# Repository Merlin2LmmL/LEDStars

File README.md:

# LEDStars

A snowflake-shaped Christmas ornament that is its own circuit board. It hangs on a tree branch, has 25 LEDs and runs
on a coin cell. I'm making about ten of them as Christmas presents for my family.

License: CERN-OHL-S-2.0 · Author: Merlin2LmmL

*A Blender render of the ornament hanging from a fir twig. You're looking at the back of the board, where the light comes out. More colours and angles are in the [gallery](#gallery).*

## What it is

Five arms with five LEDs each (red, yellow, white, blue and green), a CH32V003 microcontroller in the middle and a CR2032
holder. The LEDs are reverse-mount parts: they sit on the front of the board and shine through a small hole in the PCB,
so from the back you only see glowing dots. The battery, chip and everything else stay on the side that faces the tree.

- **Microcontroller:** WCH CH32V003F4P6, a tiny 48 MHz RISC-V chip in a TSSOP-20.
- **LEDs:** 25 XL-3216 reverse-mount LEDs (1206). The chip lights one arm at a time and cycles through them quickly, so 25 LEDs don't need 25 pins. Each colour has its own resistor because the colours need different currents.
- **Power:** a CR2032 in an SMD holder, with a 100 nF capacitor next to the chip.
- **Controls:** a button to change the lighting mode and a three-position slide switch for on, off and clock.
- **Programming:** three bare pads for SWIO (`J1`). There is no header, you just hold jumper wires on the pads while flashing with a WCH-LinkE.
- **Size:** about 99 × 95 mm, just under JLCPCB's 100 × 100 mm limit, with a hang hole in the top arm.
- **3D model:** [`hardware/LEDStar.step`](hardware/LEDStar.step), the full assembled board with all components, exported from KiCad. There is no case or other mechanical part, so the CAD source is the KiCad project in [`hardware/`](hardware/) ([`LEDStars.kicad_pcb`](hardware/LEDStars.kicad_pcb), [`LEDStars.kicad_sch`](hardware/LEDStars.kicad_sch) and [`LEDStars.kicad_pro`](hardware/LEDStars.kicad_pro)).

It's still only a design. No board has been ordered yet and there's no firmware in this repo.

## Gallery

Open a colour set and click any picture for the full-size image (2400 × 1600). Every set has a front, a left and a right view.

<details open>
<summary><b>White + yellow</b></summary>

<p>

</p>
<p><i>front · left · right</i></p>

</details>

<details>
<summary><b>White + blue</b></summary>

<p>

</p>
<p><i>front · left · right</i></p>

</details>

<details>
<summary><b>Red + green</b></summary>

<p>

</p>
<p><i>front · left · right</i></p>

</details>

### How the renders are made

The board comes straight from the KiCad file (`kicad-cli pcb export glb`). The tree is built from the CC0 *Fir Sapling*
scans by [Poly Haven](https://polyhaven.com/a/fir_sapling). The ornament isn't posed by hand: it's a rigid body with
gravity, hanging on a simulated string that runs through the hang hole and over a real twig. Each image is rendered in
Blender 4.5 (Cycles, 512 samples, OpenImageDenoise) and takes about three minutes on my RX 9070 XT.

| File | What |
|---|---|
| [`render/gallery/`](render/gallery/) | the 9 final images |
| [`LEDStar_hanging_physics.blend`](https://github.com/Merlin2LmmL/LEDStars/releases/latest/download/LEDStar_hanging_physics.blend) | the Blender scene (82 MB, on the [Releases](https://github.com/Merlin2LmmL/LEDStars/releases) page). Open it in Blender 4.5 or newer and press Play to watch the ornament drop and settle |
| [`render/scene.py`](render/scene.py) | builds the whole scene from the board export |
| [`render/README.md`](render/README.md) | how to rebuild it, plus credits |

## Build journal

I wrote down how the project went in [`JOURNAL.md`](JOURNAL.md): what I tried, what I changed my mind about and why.
It reads best from the top, since the entries are in the order things happened. If a later entry contradicts an
earlier one, the later one is right (I changed the chip, for example).

| # | Entry | What it covers |
|---|---|---|
| 1 | [November 17, 2026: Getting the Idea](JOURNAL.md#november-17-2026-getting-the-idea) | Why a snowflake ornament as a gift, and what existing kits looked like |
| 2 | [November 17, 2026 (entry 2): Deciding what the star has to be](JOURNAL.md#november-17-2026-entry-2-deciding-what-the-star-has-to-be) | The requirements: coin cell, no recharging, no through-hole parts, and the first chip (ATtiny404) |
| 3 | [November 17, 2026 (entry 3): Reconsidering my life choises](JOURNAL.md#november-17-2026-entry-3-reconsidering-my-life-choises) | Checking the parts catalogue and switching to the CH32V003 |
| 4 | [November 17, 2026 (entry 4): Deciding on the PCB Outline and LED ordering](JOURNAL.md#november-17-2026-entry-4-deciding-on-the-pcb-outline-and-led-ordering) | The board outline, LED colour order and net classes |
| 5 | [November 17, 2026 (entry 5): Routing the first version](JOURNAL.md#november-17-2026-entry-5-routing-the-first-version) | Placing the parts and routing the first version |
| 6 | [November 17, 2026 (entry 6): Letting the LEDs shine through the board](JOURNAL.md#november-17-2026-entry-6-letting-the-leds-shine-through-the-board) | Reverse-mount LEDs that shine through the board |
| 7 | [November 17, 2026 (entry 7): Reconsidering my life choises ... part 2](JOURNAL.md#november-17-2026-entry-7-reconsidering-my-life-choises--part-2) | Turning the star into a snowflake |
| 8 | [November 17, 2026 (entry 8): Back silkscreen, the repo and JLCPCB being a pain in the ass](JOURNAL.md#november-17-2026-entry-8-back-silkscreen-the-repo-and-jlcpcb-being-a-pain-in-the-ass) | Back silkscreen, the repo, and JLCPCB's Economic assembly saying no |
| 9 | [November 17, 2026 (entry 9): Doing some heavy blender rendering](JOURNAL.md#november-17-2026-entry-9-doing-some-heavy-blender-rendering) | The physics-based Blender renders |
| 10 | [November 18, 2026: Added 3 pos switch and mode switch](JOURNAL.md#november-18-2026-added-3-pos-switch-and-mode-switch) | The mode button and the ON / OFF / CLOCK slide switch I forgot at first |

## License

[CERN-OHL-S-2.0](LICENSE). If you build on this design, share your changes under the same license.

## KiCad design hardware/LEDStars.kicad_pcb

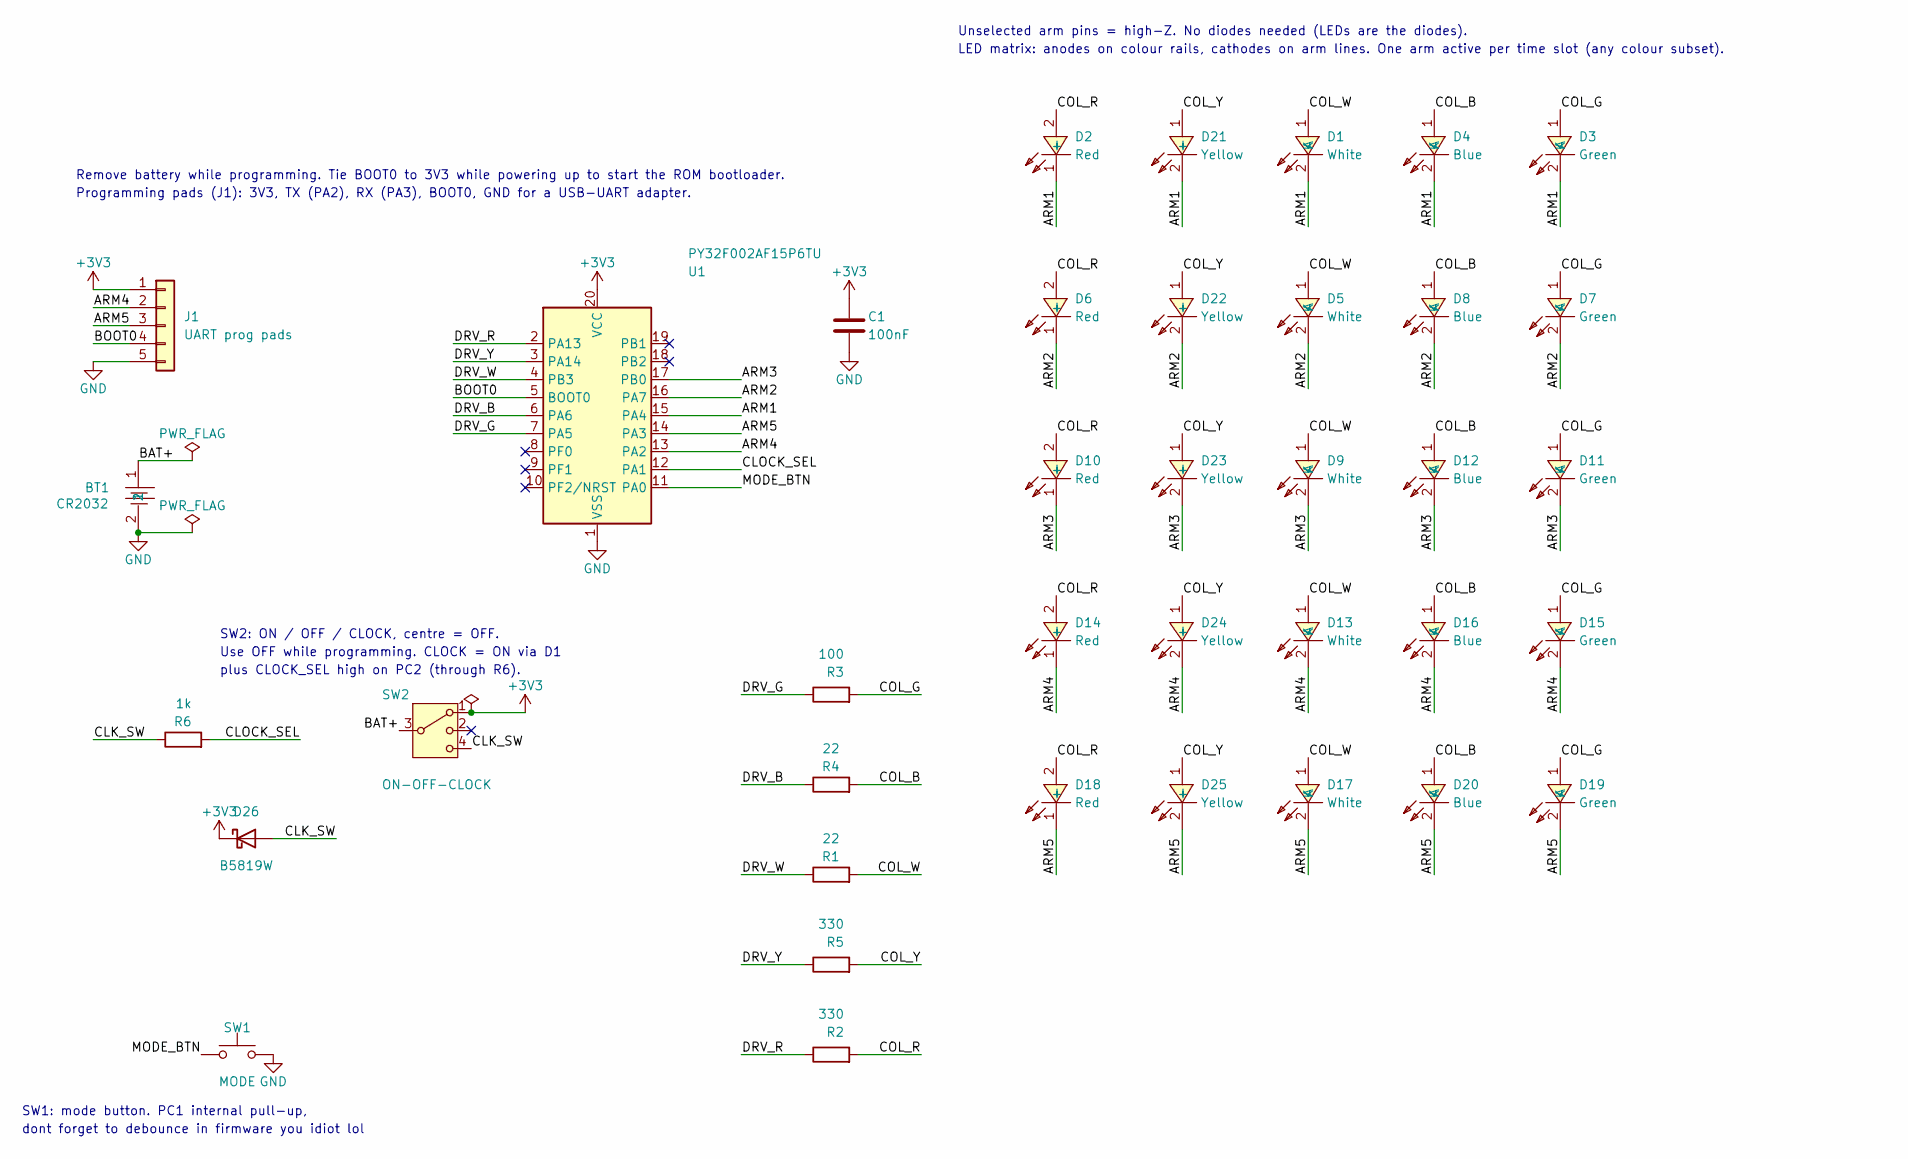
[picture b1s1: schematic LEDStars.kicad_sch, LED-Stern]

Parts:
BT1: CR2032; BAT-SMD_BS-10-B2AA010; MPN BS-10-B2AA010; LCSC Part C964798
C1: 100nF; C0603; Tolerance 10%; Voltage 50V; MPN CC0603KRX7R9BB104; LCSC Part C14663
D1, D5, D9, D13, D17: White; LED1206-RM_XL-3216; MPN KT-0805W; LCSC Part C3646935
D2, D6, D10, D14, D18: Red; LED1206-RM_XL-3216_K1; MPN NCD0805R1; LCSC Part C3646938
D3, D7, D11, D15, D19: Green; LED1206-RM_XL-3216; MPN KT-0805G; LCSC Part C3646937
D4, D8, D12, D16, D20: Blue; LED1206-RM_XL-3216; MPN KT-0805B; LCSC Part C3646941
D21, D22, D23, D24, D25: Yellow; LED1206-RM_XL-3216; MPN KT-0805Y; LCSC Part C3646939
D26: B5819W; D_SOD-123; MPN B5819W SL; LCSC Part C8598
J1: UART prog pads; UART_Pads_1x05_Staggered
R1, R4: 22; R0603; Tolerance 1%; Voltage 75V; MPN 0603WAF220JT5E; LCSC Part C23345
R2, R5: 330; R0603; Tolerance 1%; Voltage 75V; MPN 0603WAF3300T5E; LCSC Part C23138
R3: 100; R0603; Tolerance 1%; Voltage 75V; MPN 0603WAF1000T5E; LCSC Part C22775
R6: 1k; R0603; MPN 0603WAF1001T5E; LCSC Part C21190
SW1: MODE; KEY-SMD_L4.0-W3.0-LS4.9-1; MPN 3x4x2-2P-1.6N; LCSC Part C49234124
SW2: ON-OFF-CLOCK; SW-SMD_MSK13C02-SZ; MPN MSK13C02; LCSC Part C2681567
U1: PY32F002AF15P6TU; TSSOP-20_L6.5-W4.4-P0.65-LS6.4-BL; MPN PY32F002AF15P6TU; LCSC Part C5292059

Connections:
/ARM1: D1.2 (K), D2.1 (-), D3.2 (K), D4.2 (K), D21.2 (-), U1.15 (PA4)
/ARM2: D5.2 (K), D6.1 (-), D7.2 (K), D8.2 (K), D22.2 (-), U1.16 (PA7)
/ARM3: D9.2 (K), D10.1 (-), D11.2 (K), D12.2 (K), D23.2 (-), U1.17 (PB0)
/ARM4: D13.2 (K), D14.1 (-), D15.2 (K), D16.2 (K), D24.2 (-), J1.2, U1.13 (PA2)
/ARM5: D17.2 (K), D18.1 (-), D19.2 (K), D20.2 (K), D25.2 (-), J1.3, U1.14 (PA3)
/BOOT0: J1.4, U1.5 (BOOT0)
/CLK_SW: D26.2 (A), R6.1, SW2.4
/CLOCK_SEL: R6.2, U1.12 (PA1)
/COL_B: D4.1 (A), D8.1 (A), D12.1 (A), D16.1 (A), D20.1 (A), R4.2
/COL_G: D3.1 (A), D7.1 (A), D11.1 (A), D15.1 (A), D19.1 (A), R3.2
/COL_R: D2.2 (+), D6.2 (+), D10.2 (+), D14.2 (+), D18.2 (+), R2.2
/COL_W: D1.1 (A), D5.1 (A), D9.1 (A), D13.1 (A), D17.1 (A), R1.2
/COL_Y: D21.1 (+), D22.1 (+), D23.1 (+), D24.1 (+), D25.1 (+), R5.2
/DRV_B: R4.1, U1.6 (PA6)
/DRV_G: R3.1, U1.7 (PA5)
/DRV_R: R2.1, U1.2 (PA13)
/DRV_W: R1.1, U1.4 (PB3)
/DRV_Y: R5.1, U1.3 (PA14)
/MODE_BTN: SW1.1, U1.11 (PA0)

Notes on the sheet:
LED matrix: anodes on colour rails, cathodes on arm lines. One arm active per time slot (any colour subset).
SW2: ON / OFF / CLOCK, centre = OFF.
SW1: mode button. PC1 internal pull-up,
Use OFF while programming. CLOCK = ON via D1
plus CLOCK_SEL high on PC2 (through R6).
Programming pads (J1): 3V3, TX (PA2), RX (PA3), BOOT0, GND for a USB-UART adapter.
Remove battery while programming. Tie BOOT0 to 3V3 while powering up to start the ROM bootloader.
dont forget to debounce in firmware you idiot lol
Unselected arm pins = high-Z. No diodes needed (LEDs are the diodes).

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
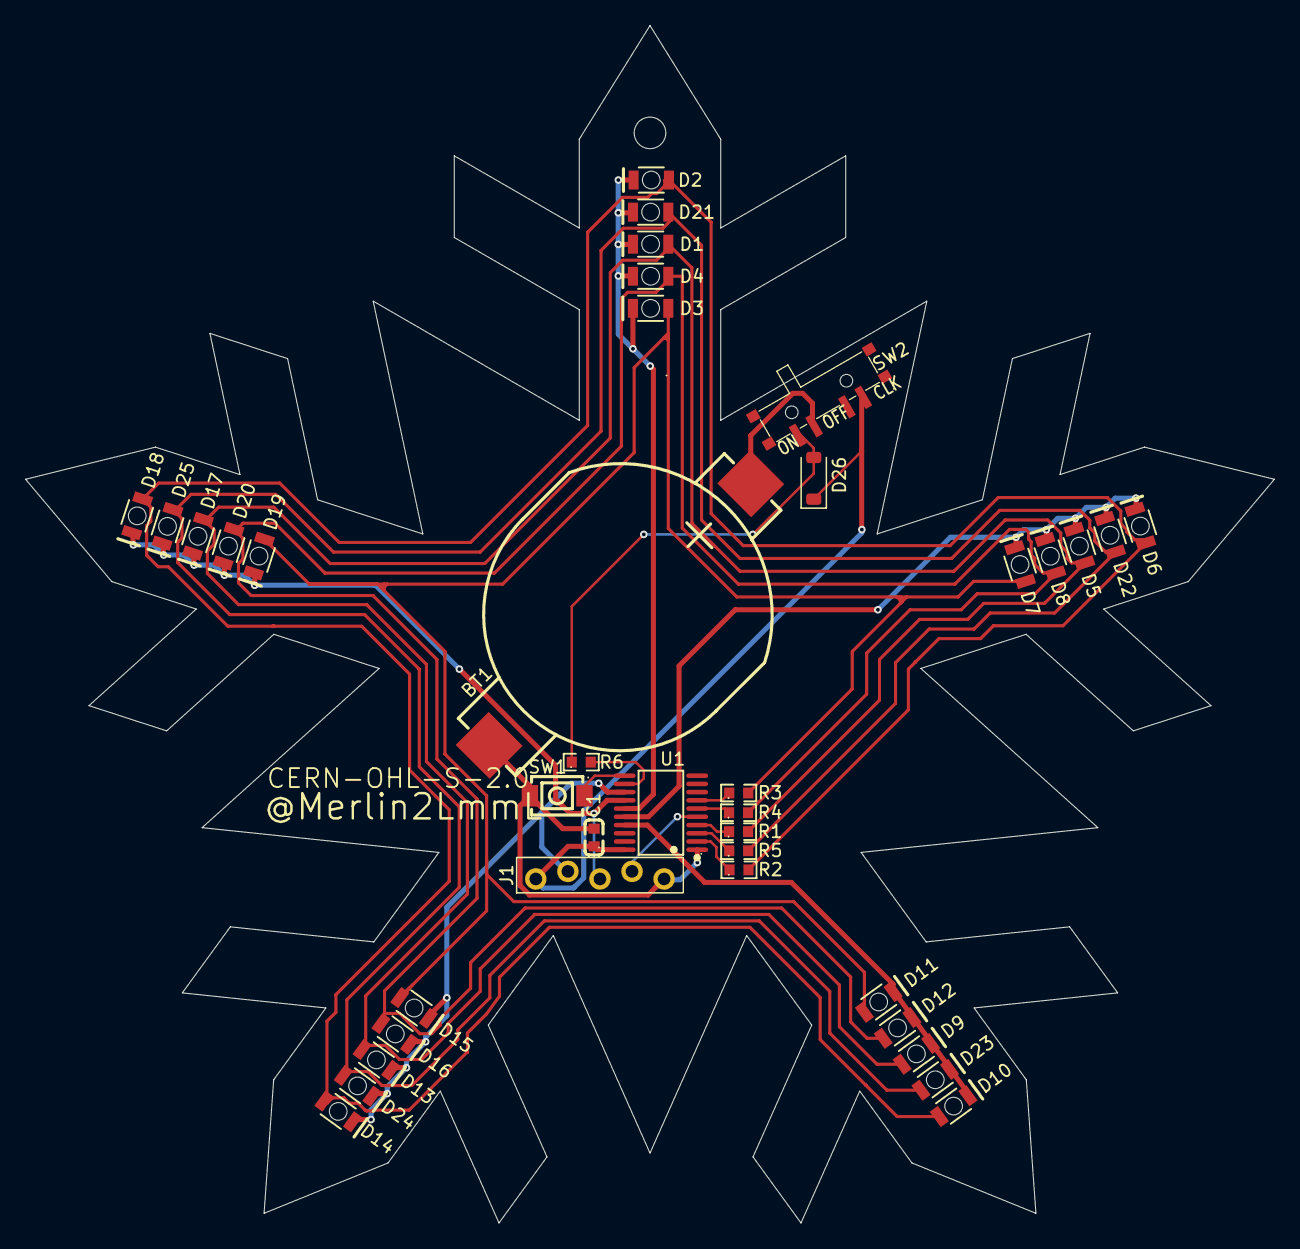
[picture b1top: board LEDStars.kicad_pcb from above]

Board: 2 copper layers, 98.9 x 94.8 mm, 38 parts (0 on the bottom side), 22 nets.

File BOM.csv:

References,Description,Vendor,MPN,LCSC,JLC class,Qty per board,Qty for 10 boards,Unit price USD (est.),Line total USD (est.),Link
-,"PCB, white solder mask, 1.6 mm, OSP (JLCPCB, order LEDStars_Y20)",JLCPCB,,,,1,10,1.50,15.00,https://jlcpcb.com/
-,Solder paste Sn99Ag0.3Cu0.7 (35 g) + flux (10 g) bundle,AliExpress,,,,1,1,EUR 11.19,EUR 11.19,https://de.aliexpress.com/item/1005009348891918.html
U1,"Microcontroller, RISC-V, TSSOP-20",LCSC,CH32V003F4P6,C5187096,Extended,1,10,0.3085,3.08,https://www.lcsc.com/product-detail/C5187096.html
BT1,"CR2032 battery holder, SMD",LCSC,BS-10-B2AA010,C964798,Extended,1,10,0.4598,4.60,https://www.lcsc.com/product-detail/C964798.html
"D1, D5, D9, D13, D17","White LED, reverse-mount 1206",LCSC,XL-3216UWC-FB,C3646935,Extended,5,50,0.0165,0.83,https://www.lcsc.com/product-detail/C3646935.html
"D21, D22, D23, D24, D25","Yellow LED, reverse-mount 1206",LCSC,XL-3216UYC-FB,C3646939,Extended,5,50,0.0159,0.80,https://www.lcsc.com/product-detail/C3646939.html
"D2, D6, D10, D14, D18","Red LED, reverse-mount 1206",LCSC,XL-3216SURC-FB,C3646938,Extended,5,50,0.0105,0.53,https://www.lcsc.com/product-detail/C3646938.html
"D3, D7, D11, D15, D19","Green LED, reverse-mount 1206",LCSC,XL-3216UGC-FB,C3646937,Extended,5,50,0.0101,0.51,https://www.lcsc.com/product-detail/C3646937.html
"D4, D8, D12, D16, D20","Blue LED, reverse-mount 1206",LCSC,XL-3216UBC-FB,C3646941,Extended,5,50,0.0146,0.73,https://www.lcsc.com/product-detail/C3646941.html
SW2,3-position slide switch (ON / OFF / CLOCK),LCSC,MSK13C02,C2681567,Extended,1,10,0.1169,1.17,https://www.lcsc.com/product-detail/C2681567.html
SW1,"Tactile button (mode), 3x4 mm",LCSC,HX 3x4x2-2P-1.6N TACTILE SWITCH,C49234124,Extended,1,10,0.0254,0.25,https://www.lcsc.com/product-detail/C49234124.html
D26,Schottky diode 40 V 1 A (CLOCK position power),LCSC,B5819W SL,C8598,Basic,1,10,0.0262,0.26,https://www.lcsc.com/product-detail/C8598.html
C1,100 nF 50 V X7R 0603 capacitor,LCSC,CL10B104KB8NNNC,C1591,Extended,1,10,0.0071,0.07,https://www.lcsc.com/product-detail/C1591.html
"R1, R4",22 Ω 0603 resistor,LCSC,0603WAF220JT5E,C23345,Basic,2,20,0.0017,0.03,https://www.lcsc.com/product-detail/C23345.html
R3,100 Ω 0603 resistor,LCSC,0603WAF1000T5E,C22775,Basic,1,10,0.0023,0.02,https://www.lcsc.com/product-detail/C22775.html
"R2, R5",330 Ω 0603 resistor,LCSC,0603WAF3300T5E,C23138,Basic,2,20,0.0020,0.04,https://www.lcsc.com/product-detail/C23138.html
R6,1 kΩ 0603 resistor,LCSC,0603WAF1001T5E,C21190,Basic,1,10,0.0017,0.02,https://www.lcsc.com/product-detail/C21190.html
-,"LCSC shipping (Global Direct Standard Line, 10-18 days)",LCSC,,,,1,1,,10.97,cost/LCSC_cart.png
-,LCSC handling fee,LCSC,,,,1,1,,3.00,cost/LCSC_cart.png
-,LCSC discount,LCSC,,,,1,1,,-0.41,cost/LCSC_cart.png
-,JLCPCB shipping (estimate for this order alone),JLCPCB,,,,1,1,,14.61,cost/JLCPCB_cart.png
-,AliExpress shipping,AliExpress,,,,1,1,,free,cost/Aliexpress_cart.png
-,AliExpress import duties,AliExpress,,,,1,1,,EUR 5.95,cost/Aliexpress_cart.png
